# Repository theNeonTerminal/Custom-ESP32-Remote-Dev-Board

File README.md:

# ESP32 Based RC dev board

A project I made to experiment more with custom ESP32 dev boards and PCBs 100% suited to specific project needs

---

## About this project

This project features 2 PCBs each running its own ESP32 chip. The first board is small in size and is the receiver board - this will go into the device you are trying to control wirelessly. It has an ESP32 Chip (with its PCB Antenna) 2 TB6612FNG Motor drivers, capable of driving upto 4 motors individually in both directions along with PWM speed control, extra headers to attack servos, extra GPIO in the form of header to connects LEDs and other peripherals as needed. The second board contains another ESP32 chip, an ADS1115 ADC connected to 2 joysticks and few push buttons for various other tasks.

From the firmware side, this runs an ESP NOW script allowing seamless and easy wireless control over both. They run a 2 way communication script

> [!NOTE]
> Both boards have a type C port for programming along, the receiver board has an extra 2 pin terminal block for external power to motors, along with a jumper that allows the ESP32 to be powered via external soruce or USB, useful for debugging.

## Hardware Design

### 01 / 3D View

<div align="center">

**RX Board**

**TX Board**

</div>

> [!NOTE]
> Schematic and footprint PDF availbale in the /ESP_-X_Board/View/

---

## BoM (Bill of Materials)

Also availbale in `./ESP32 RX Board.csv` and `./ESP32 TX Board.csv` if needed in CSV with proper footprints

### ESP32 RX Board

| Reference | Qty | Component / Value | Footprint |
|:---|:---:|:---|:---|
| C1, C2, C8 | 3 | 10µF | `C_0603_1608Metric` |
| C3, C4, C6, C7 | 4 | 0.1µF | `C_0603_1608Metric` |
| C5 | 1 | 4.7µF | `C_0603_1608Metric` |
| C9, C10 | 2 | 10µF (THT) | `CP_Radial_D10.0mm` |
| C11, C_TB1 | 2 | 0.1µF (THT) | `C_Disc_D3.4mm` |
| D1, D2, D3 | 3 | LED (SMD) | `LED_0603_1608Metric` |
| J1 | 1 | USB-C Receptacle | `USB4105-xx-A` |
| J2 | 1 | 2-Pin Header | `PinHeader_1x02` |
| J3 | 1 | 2-Pin Screw Terminal | `MX126-5.0-02P` |
| J4–J7 | 4 | 2-Pin Screw Terminal | `MX126-5.0-02P` |
| J8 | 1 | 16-Pin Socket | `PinSocket_1x16` |
| M1–M4 | 4 | Servo Connector (3-Pin) | `PinHeader_1x03` |
| Q1, Q2 | 2 | SS8050 | `SOT-23` |
| R1, R7 | 2 | 330Ω | `R_0603_1608Metric` |
| R2, R3 | 2 | 5.1kΩ | `R_0603_1608Metric` |
| R4 | 1 | 47.5kΩ | `R_0603_1608Metric` |
| R5 | 1 | 22.1kΩ | `R_0603_1608Metric` |
| R6, R13 | 2 | 1kΩ | `R_0603_1608Metric` |
| R8–R12 | 5 | 10kΩ | `R_0603_1608Metric` |
| SW1 | 1 | Reset Switch | `CK_PTS636Sx25SMTRLFS` |
| SW2 | 1 | Boot Switch | `CK_PTS636Sx25SMTRLFS` |
| U1 | 1 | AMS1117-3.3 | `SOT-223-3` |
| U2 | 1 | CP2102N-Axx-xQFN28 | `QFN-28-1EP` |
| U3 | 1 | USBLC6-2SC6 | `SOT-23-6` |
| U4 | 1 | ESP32-WROOM-32 | `ESP32-WROOM-32` |
| U5 | 1 | L7805 | `TO-220-3` |
| U6, U7 | 2 | TB6612FNG | `SSOP-24` |
| U8 | 1 | 74HC595 | `DIP-16_W7.62mm` |

### ESP32 TX Board

| Reference | Qty | Component / Value | Footprint |
|:---|:---:|:---|:---|
| BT1 | 1 | Battery | `BatteryHolder_MPD_BH-18650-PC` |
| C1, C2, C8, C12 | 4 | 10µF | `C_0603_1608Metric` |
| C3, C4, C6, C7, C9, C10, C11, C13 | 8 | 0.1µF | `C_0603_1608Metric` |
| C5 | 1 | 4.7µF | `C_0603_1608Metric` |
| D2, D5 | 2 | LED (SMD) | `LED_0603_1608Metric` |
| DP1–DP4 | 4 | Push Button | `SW_PUSH_6mm` |
| D_G1, D_R1, L1–L4 | 6 | LED (5mm THT) | `LED_D5.0mm` |
| J1 | 1 | USB-C Receptacle | `USB4105-xx-A` |
| J2 | 1 | 2×8 Pin Socket | `PinSocket_2x08` |
| Q1, Q2 | 2 | SS8050 | `SOT-23` |
| Q3 | 1 | FS8205A | `SOP65P640X120-8N` |
| R1 | 1 | 330Ω | `R_0603_1608Metric` |
| R2, R3 | 2 | 5.1kΩ | `R_0603_1608Metric` |
| R4 | 1 | 47.5kΩ | `R_0603_1608Metric` |
| R5 | 1 | 22.1kΩ | `R_0603_1608Metric` |
| R6, R15–R18, R20–R23 | 9 | 1kΩ | `R_0603_1608Metric` |
| R7–R14 | 8 | 10kΩ | `R_0603_1608Metric` |
| R19 | 1 | 100Ω | `R_Axial_DIN0309` |
| R24–R28 | 5 | 470Ω | `R_0603_1608Metric` |
| SW1 | 1 | Reset Switch | `CK_PTS636Sx25SMTRLFS` |
| SW2 | 1 | Boot Switch | `CK_PTS636Sx25SMTRLFS` |
| SW3 | 1 | SPDT Slide Switch | `WS-SLTV` |
| U1 | 1 | AMS1117-3.3 | `SOT-223-3` |
| U2 | 1 | CP2102N-Axx-xQFN28 | `QFN-28-1EP` |
| U3 | 1 | USBLC6-2SC6 | `SOT-23-6` |
| U4 | 1 | ESP32-WROOM-32 | `ESP32-WROOM-32` |
| U5 | 1 | ADS1115IDGS | `TSSOP-10` |
| U6, U7 | 2 | Joystick Module | `JoyStick` |
| U8 | 1 | TP4056 | `SOIC-8-1EP` |
| U9 | 1 | DW01A | `SOT95P280X145-6N` |

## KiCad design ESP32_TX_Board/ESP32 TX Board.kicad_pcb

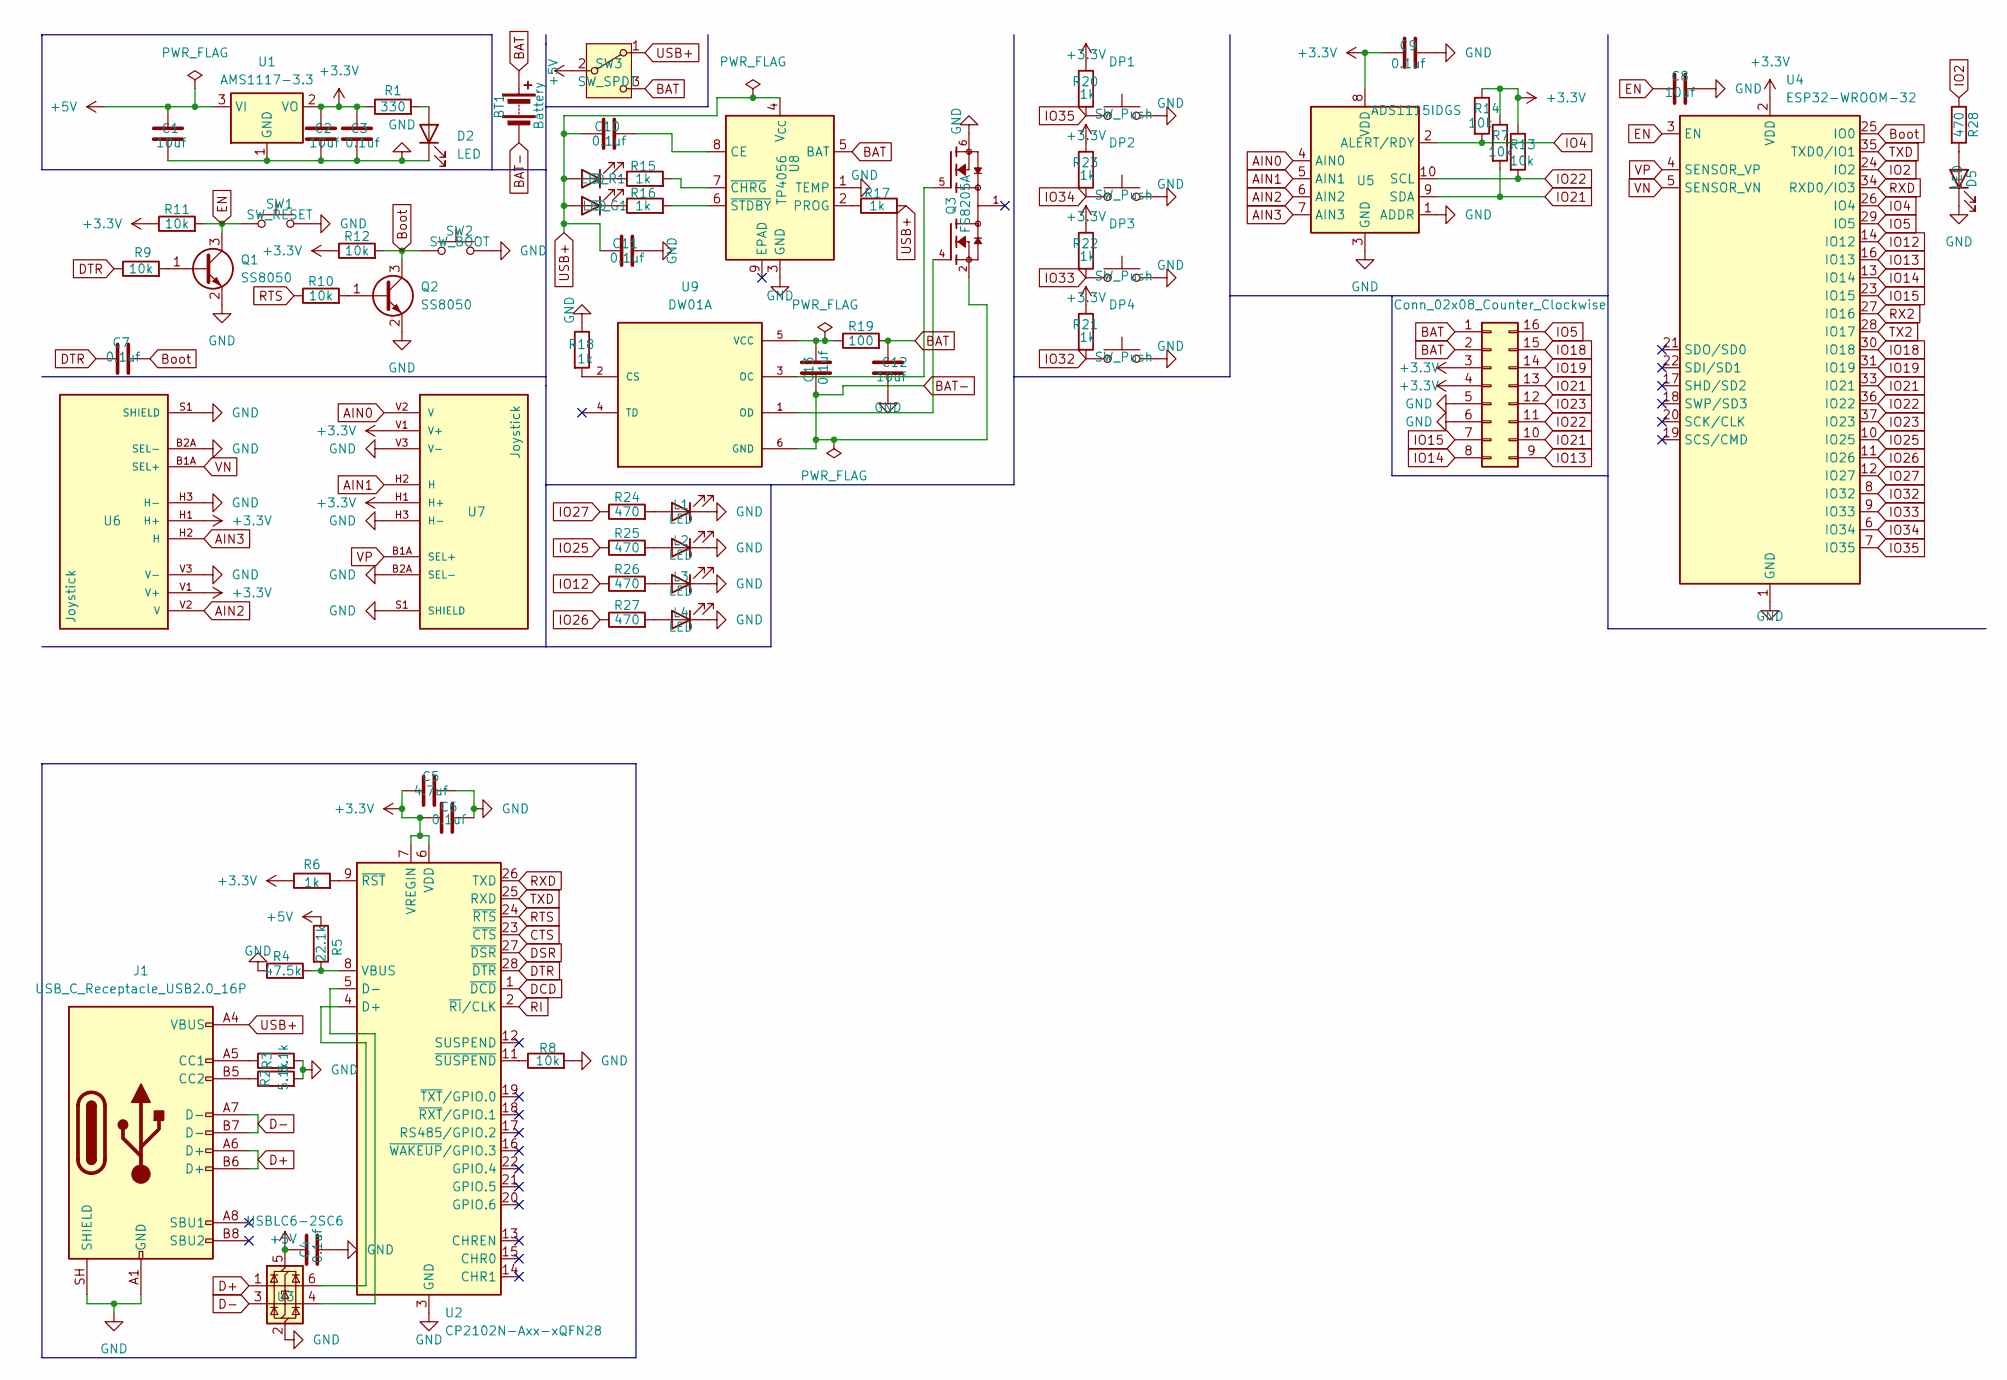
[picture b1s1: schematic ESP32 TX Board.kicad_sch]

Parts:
BT1: Battery; BatteryHolder_MPD_BH-18650-PC
C1, C2, C8, C12: 10uf; C_0603_1608Metric_Pad1.08x0.95mm_HandSolder
C3, C4, C6, C7, C9, C10, C11, C13: 0.1uf; C_0603_1608Metric_Pad1.08x0.95mm_HandSolder
C5: 4.7uf; C_0603_1608Metric_Pad1.08x0.95mm_HandSolder
D2, D5: LED; LED_0603_1608Metric_Pad1.05x0.95mm_HandSolder
DP1, DP2, DP3, DP4: SW_Push; SW_PUSH_6mm
D_G1: LED; LED_D5.0mm
D_R1: LED; LED_D5.0mm
J1: USB_C_Receptacle_USB2.0_16P; USB_C_Receptacle_GCT_USB4105-xx-A_16P_TopMnt_Horizontal
J2: Conn_02x08_Counter_Clockwise; PinSocket_2x08_P2.54mm_Vertical
L1, L2, L3, L4: LED; LED_D5.0mm
Q1, Q2: SS8050; SOT-23
Q3: FS8205A; SOP65P640X120-8N; MPN FS8205A
R1: 330; R_0603_1608Metric_Pad0.98x0.95mm_HandSolder
R2, R3: 5.1k; R_0603_1608Metric_Pad0.98x0.95mm_HandSolder
R4: 47.5k; R_0603_1608Metric_Pad0.98x0.95mm_HandSolder
R5: 22.1k; R_0603_1608Metric_Pad0.98x0.95mm_HandSolder
R6, R15, R16, R17, R18, R20, R21, R22, R23: 1k; R_0603_1608Metric_Pad0.98x0.95mm_HandSolder
R7, R8, R9, R10, R11, R12, R13, R14: 10k; R_0603_1608Metric_Pad0.98x0.95mm_HandSolder
R19: 100; R_Axial_DIN0309_L9.0mm_D3.2mm_P12.70mm_Horizontal
R24, R25, R26, R27, R28: 470; R_0603_1608Metric_Pad0.98x0.95mm_HandSolder
SW1: SW_RESET; SW_Tactile_SPST_NO_Straight_CK_PTS636Sx25SMTRLFS
SW2: SW_BOOT; SW_Tactile_SPST_NO_Straight_CK_PTS636Sx25SMTRLFS
SW3: SW_SPDT; SW_Slide-03_Wuerth-WS-SLTV_10x2.5x6.4_P2.54mm
U1: AMS1117-3.3; SOT-223-3_TabPin2
U2: CP2102N-Axx-xQFN28; QFN-28-1EP_5x5mm_P0.5mm_EP3.35x3.35mm
U3: USBLC6-2SC6; SOT-23-6
U4: ESP32-WROOM-32
U5: ADS1115IDGS; TSSOP-10_3x3mm_P0.5mm
U6, U7: Joystick; JoyStick; PARTREV N/A
U8: TP4056; SOIC-8-1EP_3.9x4.9mm_P1.27mm_EP2.41x3.3mm_ThermalVias
U9: DW01A; SOT95P280X145-6N; MPN DW01A

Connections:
+3.3V: C2.1, C3.1, C5.1, C6.1, C9.2, J2.3, J2.4, R1.1, R6.1, R7.1, R11.1, R12.1, R13.1, R14.1, R20.1, R21.1, R22.1, R23.1, U1.2 (VO), U2.6 (VDD), U2.7 (VREGIN), U4.2 (VDD), U5.8 (VDD), U6.H1 (H+), U6.V1 (V+), U7.H1 (H+), U7.V1 (V+)
+5V: C1.1, C4.1, R5.1, SW3.2 (B), U1.3 (VI), U3.5 (VBUS)
AIN0: U5.4 (AIN0), U7.V2 (V)
AIN1: U5.5 (AIN1), U7.H2 (H)
AIN2: U5.6 (AIN2), U6.V2 (V)
AIN3: U5.7 (AIN3), U6.H2 (H)
BAT: BT1.1 (+), C12.1, J2.1, J2.2, R19.2, SW3.3 (C), U8.5 (BAT)
BAT-: BT1.2 (-), C13.1, Q3.2, Q3.3, U9.6 (GND)
Boot: C7.2, Q2.3 (C), R12.2, SW2.1, U4.25 (IO0)
CTS: U2.23 (~CTS)
D+: J1.A6 (D+), J1.B6 (D+), U3.1 (I/O1)
D-: J1.A7 (D-), J1.B7 (D-), U3.3 (I/O2)
DCD: U2.1 (~DCD)
DSR: U2.27 (~DSR)
DTR: C7.1, R9.1, U2.28 (~DTR)
EN: C8.1, Q1.3 (C), R11.2, SW1.1, U4.3 (EN)
GND: C1.2, C2.2, C3.2, C4.2, C5.2, C6.2, C8.2, C9.1, C11.2, C12.2, D2.1 (K), D5.1 (K), DP1.2, DP2.2, DP3.2, DP4.2, J1.A1 (GND), J1.A12 (GND), J1.B1 (GND), J1.B12 (GND), J1.SH (SHIELD), J2.5, J2.6, L1.1 (K), L2.1 (K), L3.1 (K), L4.1 (K), Q1.2 (E), Q2.2 (E), Q3.6, Q3.7, R2.2, R3.2, R4.1, R8.2, R18.1, SW1.2, SW2.2, U1.1 (GND), U2.3 (GND), U2.29 (GND), U3.2 (GND), U4.1 (GND), U4.15 (GND), U4.38 (GND), U4.39 (GND), U5.1 (ADDR), U5.3 (GND), U6.B2A (SEL-), U6.H3 (H-), U6.S1 (SHIELD), U6.S2 (SHIELD), U6.S3 (SHIELD), U6.S4 (SHIELD), U6.V3 (V-), U7.B2A (SEL-), U7.H3 (H-), U7.S1 (SHIELD), U7.S2 (SHIELD), U7.S3 (SHIELD), U7.S4 (SHIELD), U7.V3 (V-), U8.1 (TEMP), U8.3 (GND)
IO2: R28.1, U4.24 (IO2)
IO4: R14.2, U4.26 (IO4), U5.2 (ALERT/RDY)
IO5: J2.16, U4.29 (IO5)
IO12: R26.1, U4.14 (IO12)
IO13: J2.9, U4.16 (IO13)
IO14: J2.8, U4.13 (IO14)
IO15: J2.7, U4.23 (IO15)
IO18: J2.15, U4.30 (IO18)
IO19: J2.14, U4.31 (IO19)
IO21: J2.10, J2.13, R7.2, U4.33 (IO21), U5.9 (SDA)
IO22: J2.11, R13.2, U4.36 (IO22), U5.10 (SCL)
IO23: J2.12, U4.37 (IO23)
IO25: R25.1, U4.10 (IO25)
IO26: R27.1, U4.11 (IO26)
IO27: R24.1, U4.12 (IO27)
IO32: DP4.1, R21.2, U4.8 (IO32)
IO33: DP3.1, R22.2, U4.9 (IO33)
IO34: DP2.1, R23.2, U4.6 (IO34)
IO35: DP1.1, R20.2, U4.7 (IO35)
unnamed: D2.2 (A), R1.2
unnamed: D5.2 (A), R28.2
unnamed: D_G1.1 (K), R15.1
unnamed: D_R1.1 (K), R16.1
unnamed: J1.A5 (CC1), R3.1
unnamed: J1.B5 (CC2), R2.1
unnamed: L1.2 (A), R24.2
unnamed: L2.2 (A), R25.2
unnamed: L3.2 (A), R26.2
unnamed: L4.2 (A), R27.2
unnamed: Q1.1 (B), R9.2
unnamed: Q2.1 (B), R10.2
unnamed: U2.4 (D+), U3.6 (I/O1)
unnamed: U2.5 (D-), U3.4 (I/O2)
unnamed: R4.2, R5.2, U2.8 (VBUS)
unnamed: R6.2, U2.9 (~RST)
unnamed: R8.1, U2.11 (~SUSPEND)
unnamed: C10.2, U8.8 (CE)
unnamed: R17.1, U8.2 (PROG)
unnamed: R15.2, U8.7 (~CHRG)
unnamed: R16.2, U8.6 (~STDBY)
unnamed: R18.2, U9.2 (CS)
unnamed: Q3.5, U9.3 (OC)
unnamed: Q3.4, U9.1 (OD)
unnamed: C13.2, R19.1, U9.5 (VCC)
RI: U2.2 (~RI/CLK)
RTS: R10.1, U2.24 (~RTS)
RX2: U4.27 (IO16)
RXD: U2.26 (TXD), U4.34 (RXD0/IO3)
TX2: U4.28 (IO17)
TXD: U2.25 (RXD), U4.35 (TXD0/IO1)
USB+: C10.1, C11.1, D_G1.2 (A), D_R1.2 (A), J1.A4 (VBUS), J1.A9 (VBUS), J1.B4 (VBUS), J1.B9 (VBUS), R17.2, SW3.1 (A), U8.4 (V_{CC})
VN: U4.5 (SENSOR_VN), U6.B1A (SEL+)
VP: U4.4 (SENSOR_VP), U7.B1A (SEL+)

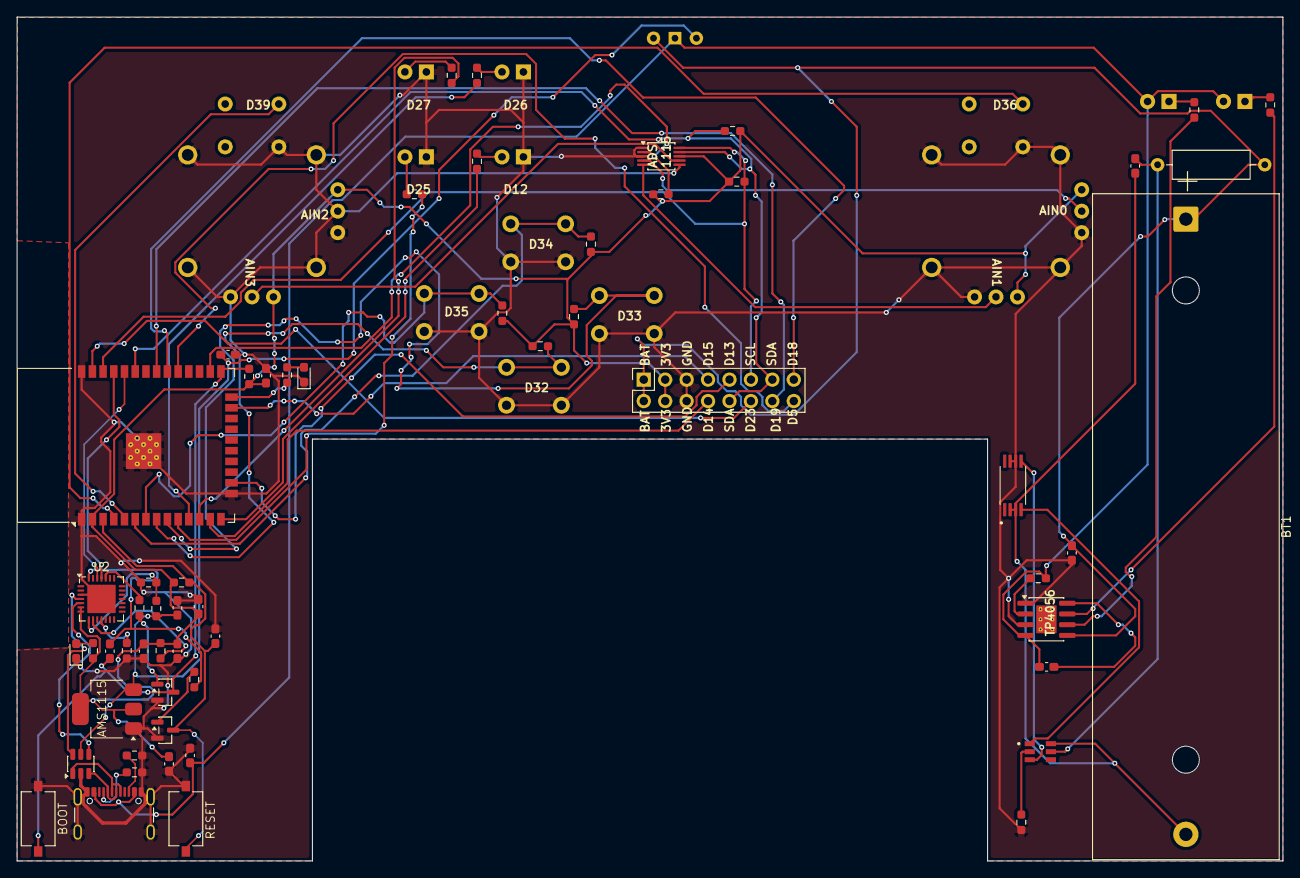
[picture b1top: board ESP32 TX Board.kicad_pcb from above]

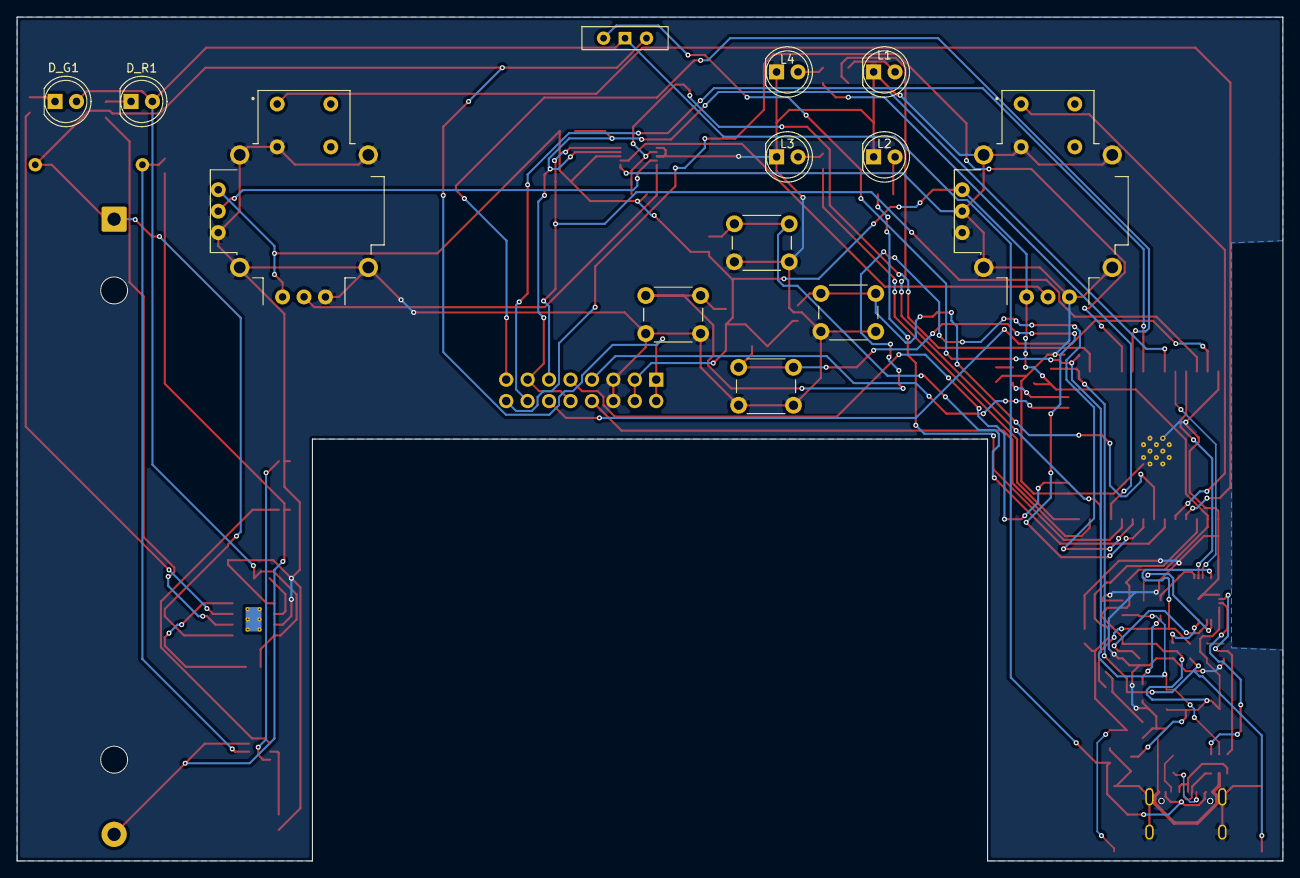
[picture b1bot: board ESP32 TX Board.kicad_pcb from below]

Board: 2 copper layers, 150.0 x 100.0 mm, 71 parts (13 on the bottom side), 64 nets.

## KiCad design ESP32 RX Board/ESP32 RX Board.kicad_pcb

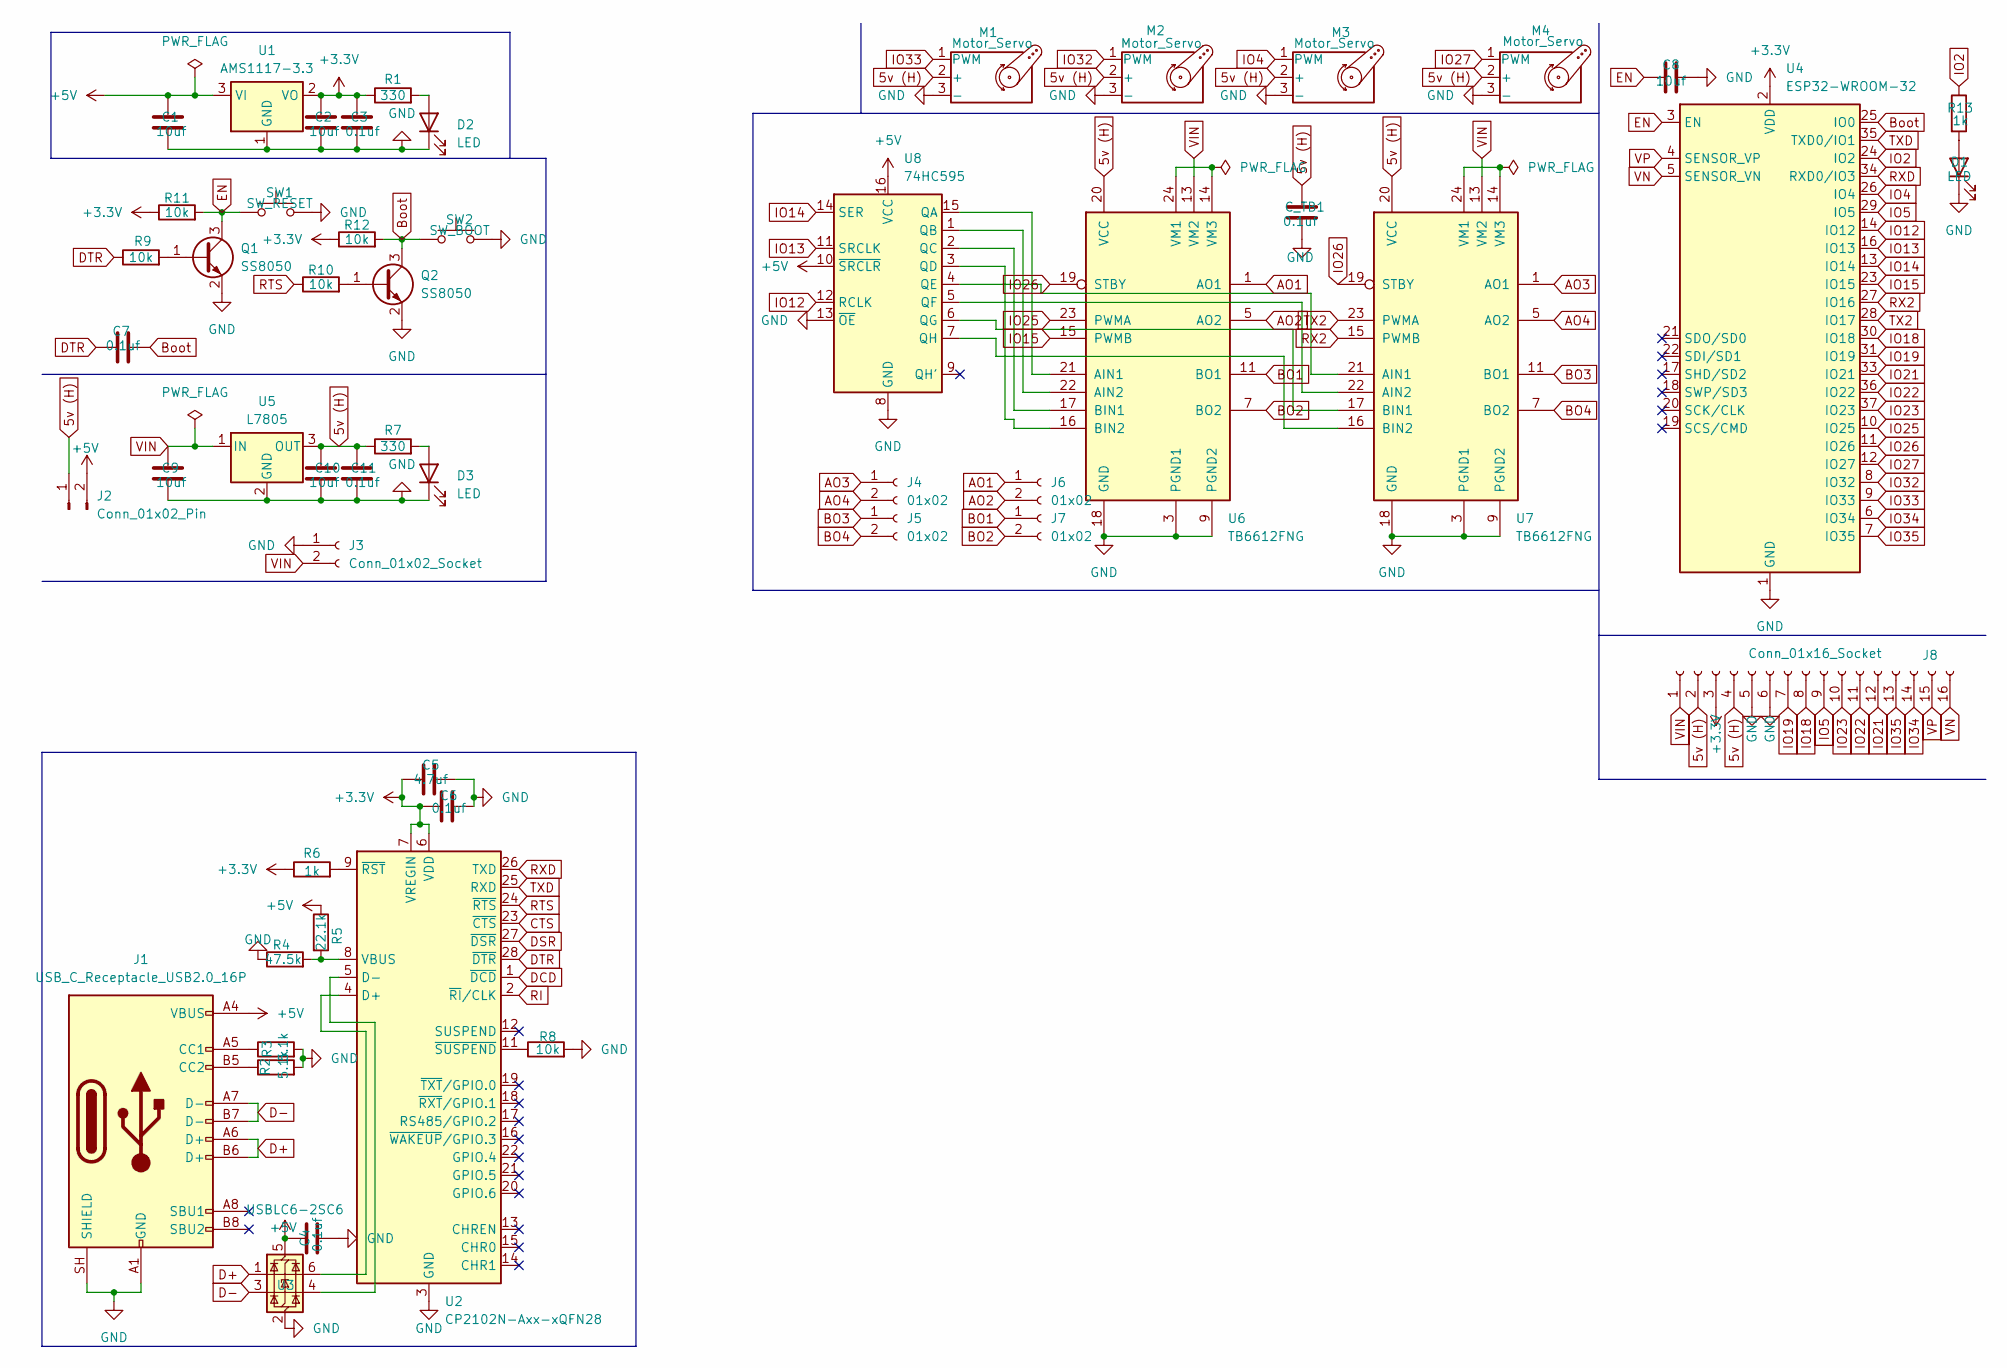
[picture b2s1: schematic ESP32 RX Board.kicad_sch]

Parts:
C1, C2, C8, C9, C10: 10uf; C_0603_1608Metric_Pad1.08x0.95mm_HandSolder
C3, C4, C6, C7, C11: 0.1uf; C_0603_1608Metric_Pad1.08x0.95mm_HandSolder
C5: 4.7uf; C_0603_1608Metric_Pad1.08x0.95mm_HandSolder
C_TB1: 0.1uf; C_Disc_D3.4mm_W2.1mm_P2.50mm
D1, D2, D3: LED; LED_0603_1608Metric_Pad1.05x0.95mm_HandSolder
J1: USB_C_Receptacle_USB2.0_16P; USB_C_Receptacle_GCT_USB4105-xx-A_16P_TopMnt_Horizontal
J2: Conn_01x02_Pin; PinHeader_1x02_P2.54mm_Vertical
J3: Conn_01x02_Socket; TerminalBlock_MaiXu_MX126-5.0-02P_1x02_P5.00mm
J4, J5, J6, J7: 01x02; TerminalBlock_MaiXu_MX126-5.0-02P_1x02_P5.00mm
J8: Conn_01x16_Socket; PinSocket_1x16_P2.54mm_Vertical
M1, M2, M3, M4: Motor_Servo; PinHeader_1x03_P2.54mm_Vertical
Q1, Q2: SS8050; SOT-23
R1, R7: 330; R_0603_1608Metric_Pad0.98x0.95mm_HandSolder
R2, R3: 5.1k; R_0603_1608Metric_Pad0.98x0.95mm_HandSolder
R4: 47.5k; R_0603_1608Metric_Pad0.98x0.95mm_HandSolder
R5: 22.1k; R_0603_1608Metric_Pad0.98x0.95mm_HandSolder
R6, R13: 1k; R_0603_1608Metric_Pad0.98x0.95mm_HandSolder
R8, R9, R10, R11, R12: 10k; R_0603_1608Metric_Pad0.98x0.95mm_HandSolder
SW1: SW_RESET; SW_Tactile_SPST_NO_Straight_CK_PTS636Sx25SMTRLFS
SW2: SW_BOOT; SW_Tactile_SPST_NO_Straight_CK_PTS636Sx25SMTRLFS
U1: AMS1117-3.3; SOT-223-3_TabPin2
U2: CP2102N-Axx-xQFN28; QFN-28-1EP_5x5mm_P0.5mm_EP3.35x3.35mm
U3: USBLC6-2SC6; SOT-23-6
U4: ESP32-WROOM-32
U5: L7805; TO-220-3_Vertical
U6, U7: TB6612FNG; SSOP-24_5.3x8.2mm_P0.65mm
U8: 74HC595; DIP-16_W7.62mm

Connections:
5v (H): C10.1, C11.1, C_TB1.1, J2.1, J8.2, J8.4, M1.2 (+), M2.2 (+), M3.2 (+), M4.2 (+), R7.1, U5.3 (OUT), U6.20 (VCC), U7.20 (VCC); also elsewhere on the board
+3.3V: C2.1, C3.1, C5.1, C6.1, J8.3, R1.1, R6.1, R11.1, R12.1, U1.2 (VO), U2.6 (VDD), U2.7 (VREGIN), U4.2 (VDD)
+5V: C1.1, C4.1, J1.A4 (VBUS), J1.A9 (VBUS), J1.B4 (VBUS), J1.B9 (VBUS), J2.2, R5.1, U1.3 (VI), U3.5 (VBUS), U8.10 (~SRCLR), U8.16 (VCC)
AO1: J6.1, U6.1 (AO1), U6.2 (AO1)
AO2: J6.2, U6.5 (AO2), U6.6 (AO2)
AO3: J4.1, U7.1 (AO1), U7.2 (AO1)
AO4: J4.2, U7.5 (AO2), U7.6 (AO2)
BO1: J7.1, U6.11 (BO1), U6.12 (BO1)
BO2: J7.2, U6.7 (BO2), U6.8 (BO2)
BO3: J5.1, U7.11 (BO1), U7.12 (BO1)
BO4: J5.2, U7.7 (BO2), U7.8 (BO2)
Boot: C7.2, Q2.3 (C), R12.2, SW2.1, U4.25 (IO0)
CTS: U2.23 (~CTS)
D+: J1.A6 (D+), J1.B6 (D+), U3.1 (I/O1)
D-: J1.A7 (D-), J1.B7 (D-), U3.3 (I/O2)
DCD: U2.1 (~DCD)
DSR: U2.27 (~DSR)
DTR: C7.1, R9.1, U2.28 (~DTR)
EN: C8.1, Q1.3 (C), R11.2, SW1.1, U4.3 (EN)
GND: C1.2, C2.2, C3.2, C4.2, C5.2, C6.2, C8.2, C9.2, C10.2, C11.2, C_TB1.2, D1.1 (K), D2.1 (K), D3.1 (K), J1.A1 (GND), J1.A12 (GND), J1.B1 (GND), J1.B12 (GND), J1.SH (SHIELD), J3.1, J8.5, J8.6, M1.3 (-), M2.3 (-), M3.3 (-), M4.3 (-), Q1.2 (E), Q2.2 (E), R2.2, R3.2, R4.1, R8.2, SW1.2, SW2.2, U1.1 (GND), U2.3 (GND), U2.29 (GND), U3.2 (GND), U4.1 (GND), U4.15 (GND), U4.38 (GND), U4.39 (GND), U5.2 (GND), U6.3 (PGND1), U6.4 (PGND1), U6.9 (PGND2), U6.10 (PGND2), U6.18 (GND), U7.3 (PGND1), U7.4 (PGND1), U7.9 (PGND2), U7.10 (PGND2), U7.18 (GND), U8.8 (GND), U8.13 (~OE); also elsewhere on the board
IO2: R13.1, U4.24 (IO2)
IO4: M3.1 (PWM), U4.26 (IO4); also elsewhere on the board
IO5: J8.9, U4.29 (IO5)
IO12: U4.14 (IO12), U8.12 (RCLK)
IO13: U4.16 (IO13), U8.11 (SRCLK)
IO14: U4.13 (IO14), U8.14 (SER)
IO15: U4.23 (IO15), U6.15 (PWMB)
IO18: J8.8, U4.30 (IO18)
IO19: J8.7, U4.31 (IO19)
IO21: J8.12, U4.33 (IO21)
IO22: J8.11, U4.36 (IO22)
IO23: J8.10, U4.37 (IO23)
IO25: U4.10 (IO25), U6.23 (PWMA)
IO26: U4.11 (IO26), U6.19 (STBY), U7.19 (STBY)
IO27: M4.1 (PWM), U4.12 (IO27); also elsewhere on the board
IO32: M2.1 (PWM), U4.8 (IO32); also elsewhere on the board
IO33: M1.1 (PWM), U4.9 (IO33); also elsewhere on the board
IO34: J8.14, U4.6 (IO34)
IO35: J8.13, U4.7 (IO35)
unnamed: D1.2 (A), R13.2
unnamed: D2.2 (A), R1.2
unnamed: D3.2 (A), R7.2
unnamed: J1.A5 (CC1), R3.1
unnamed: J1.B5 (CC2), R2.1
unnamed: Q1.1 (B), R9.2
unnamed: Q2.1 (B), R10.2
unnamed: U2.4 (D+), U3.6 (I/O1)
unnamed: U2.5 (D-), U3.4 (I/O2)
unnamed: R4.2, R5.2, U2.8 (VBUS)
unnamed: R6.2, U2.9 (~RST)
unnamed: R8.1, U2.11 (~SUSPEND)
unnamed: U6.21 (AIN1), U8.15 (QA)
unnamed: U6.22 (AIN2), U8.1 (QB)
unnamed: U6.17 (BIN1), U8.2 (QC)
unnamed: U6.16 (BIN2), U8.3 (QD)
unnamed: U6.14 (VM3), U6.24 (VM1)
unnamed: U7.21 (AIN1), U8.4 (QE)
unnamed: U7.22 (AIN2), U8.5 (QF)
unnamed: U7.17 (BIN1), U8.6 (QG)
unnamed: U7.16 (BIN2), U8.7 (QH)
unnamed: U7.14 (VM3), U7.24 (VM1)
RI: U2.2 (~RI/CLK)
RTS: R10.1, U2.24 (~RTS)
RX2: U4.27 (IO16), U7.15 (PWMB)
RXD: U2.26 (TXD), U4.34 (RXD0/IO3)
TX2: U4.28 (IO17), U7.23 (PWMA)
TXD: U2.25 (RXD), U4.35 (TXD0/IO1)
VIN: C9.1, J3.2, J8.1, U5.1 (IN), U6.13 (VM2), U7.13 (VM2)
VN: J8.16, U4.5 (SENSOR_VN)
VP: J8.15, U4.4 (SENSOR_VP)

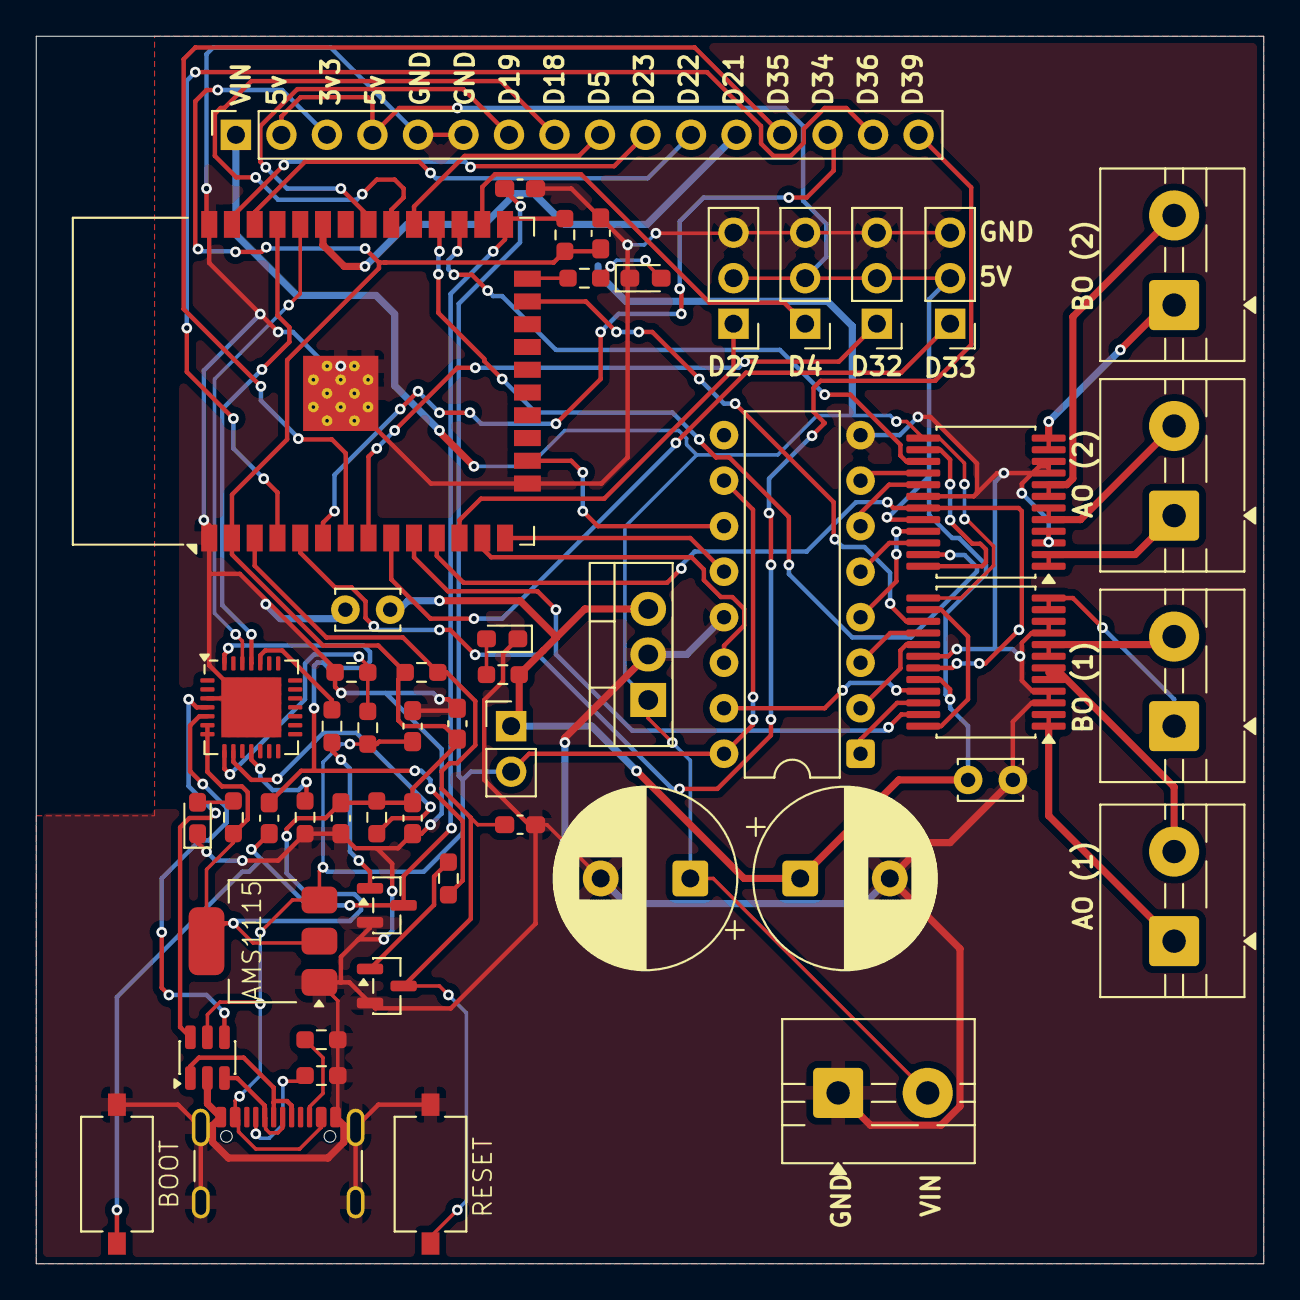
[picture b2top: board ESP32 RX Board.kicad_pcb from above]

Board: 2 copper layers, 68.5 x 68.5 mm, 52 parts (0 on the bottom side), 66 nets.

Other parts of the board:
D4, D27, D32, D33: Motor_Servo; PinHeader_1x03_P2.54mm_Vertical

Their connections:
5v (H): D4.2 (+), D27.2 (+), D32.2 (+), D33.2 (+); also elsewhere on the board
GND: D4.3 (-), D27.3 (-), D32.3 (-), D33.3 (-); also elsewhere on the board
IO4: D4.1 (PWM); also elsewhere on the board
IO27: D27.1 (PWM); also elsewhere on the board
IO32: D32.1 (PWM); also elsewhere on the board
IO33: D33.1 (PWM); also elsewhere on the board
